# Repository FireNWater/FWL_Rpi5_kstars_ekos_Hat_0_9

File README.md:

# Raspberry Pi Hat for AstroArch Version 0.9

This repository is for a Raspberry Pi Hat that provides various hardware control functions for Astrophotography equipment. 

Currently this repository only contains the KiCAD files, but I will add more photos and instructions to build your own as I progress.

Here is the link to order PCBs at OshPark:  https://oshpark.com/shared_projects/S5zMuqNM

This is the link to DigiKey Parts List: https://www.digikey.com/en/mylists/list/DTLNYIF8ZV

The DigiKey list includes 10% attrition, so depending on how good you think you are you can save a bit of money there.

The files in the "Linux Software" folder are system files and aliases to help you control the various functions of the hat.  The systemd files are written so that all of the DC power ports and Dew Heater ports turn on once the Raspberry Pi has completed its boot up.  The udev rules will allow you to control the Rpi GPIO ports from the terminal without using sudo.  The aliases, are shortcuts to turning the DC power ports and Dew Heaters on and off from a terminal.

The "libgpiod" package must be installed in order to control the GPIO pins from the command line.  To install in Arch Linux type: "sudo pacman -S libgpiod" at the command line.

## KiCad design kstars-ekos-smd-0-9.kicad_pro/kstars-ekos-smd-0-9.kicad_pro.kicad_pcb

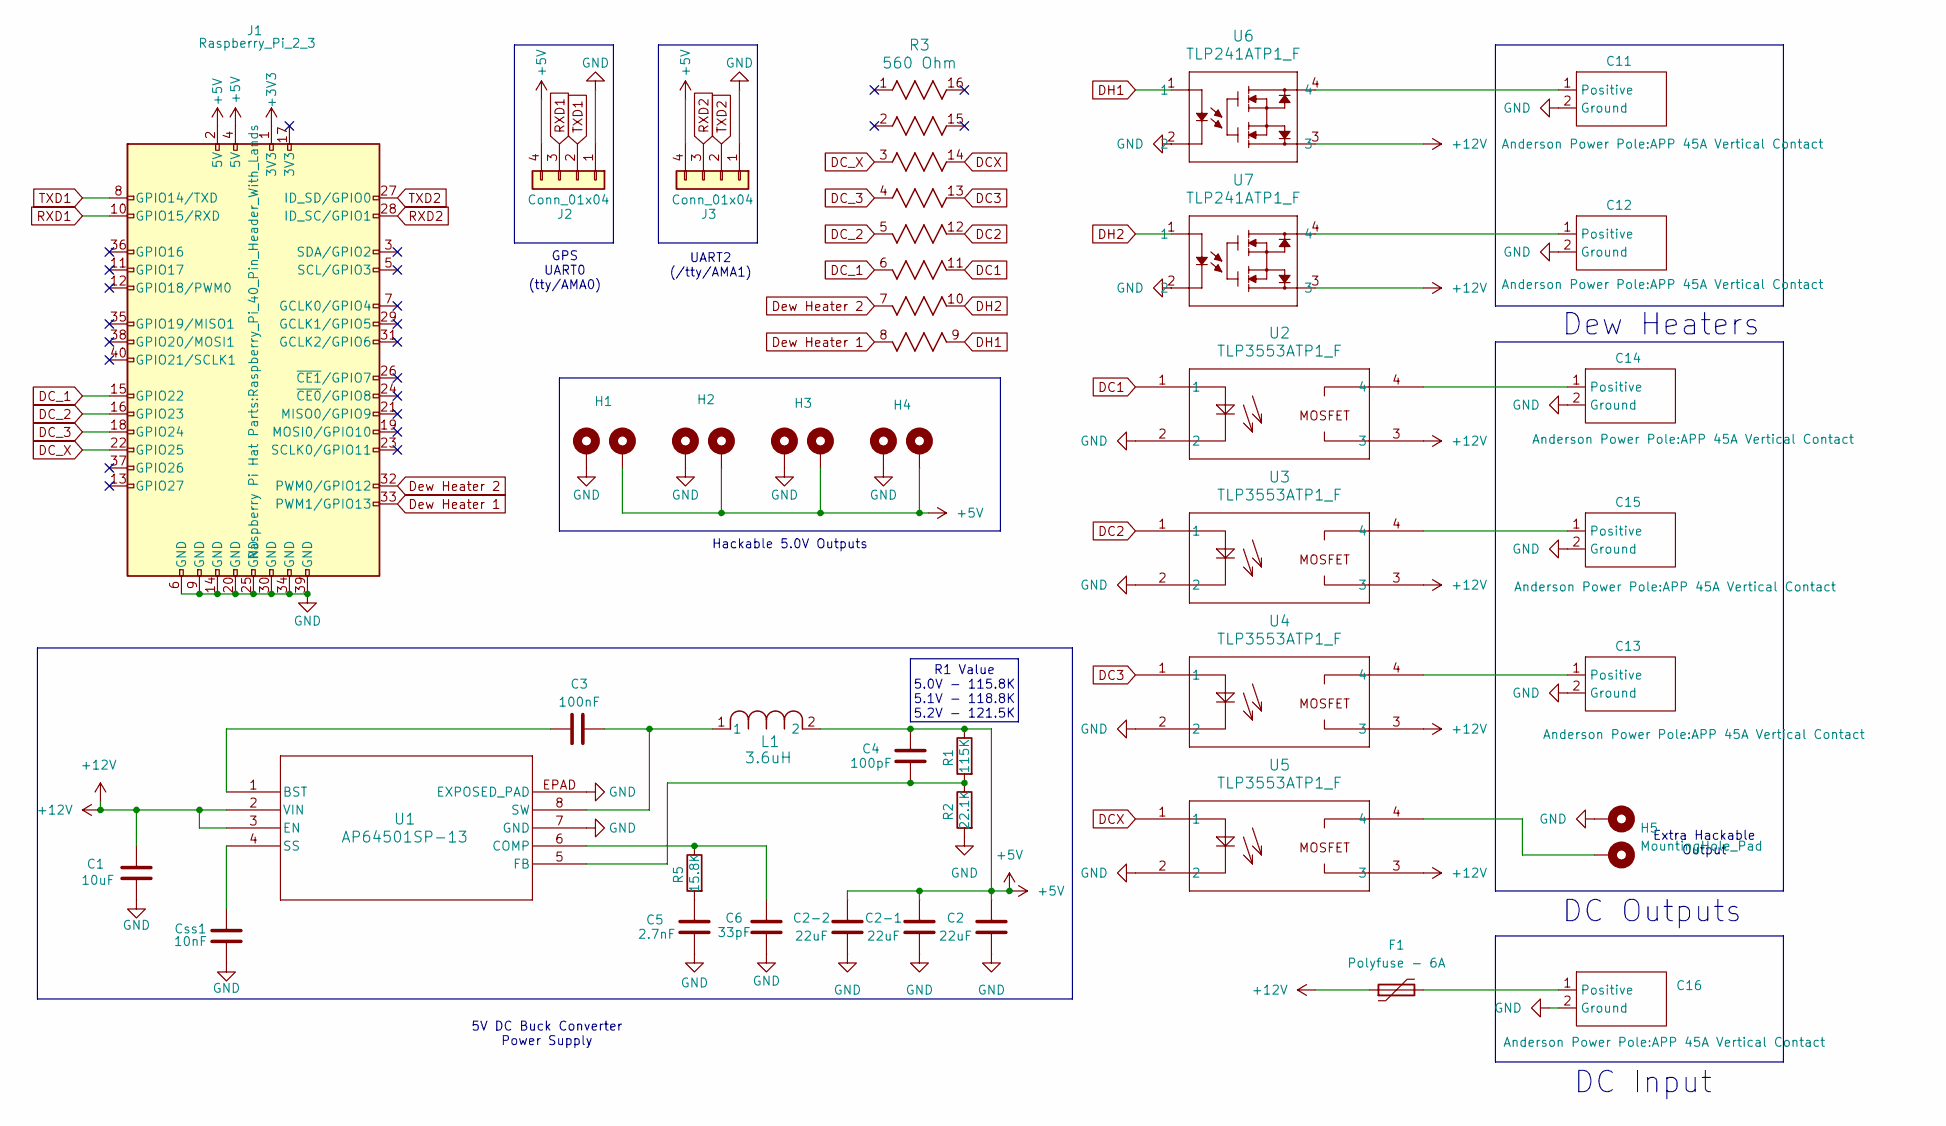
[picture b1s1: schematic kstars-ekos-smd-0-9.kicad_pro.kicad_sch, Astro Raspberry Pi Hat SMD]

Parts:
C1: 10uF; C_0805_2012Metric
C2, C2-1, C2-2: 22uF; C_0805_2012Metric
C3: 100nF; C_0805_2012Metric
C4: 100pF; C_0805_2012Metric
C5: 2.7nF; C_0805_2012Metric
C6: 33pF; C_0805_2012Metric
C11, C12, C13, C14, C15, C16: APP 45A Vertical Contact
Css1: 10nF; C_0805_2012Metric
F1: Polyfuse - 6A; Fuse_2920_7451Metric
H1, H2, H3, H4, H5: MountingHole_Pad; PinHeader_1x02_P2.54mm_Vertical
J1: Raspberry_Pi_2_3; Raspberry_Pi_40_Pin_Header_With_Lands
J2, J3: Conn_01x04; PinHeader_1x04_P2.54mm_Vertical
L1: 3.6uH; L_Cenker_CKCS8080
R1: 115K; R_0805_2012Metric
R2: 22.1K; R_0805_2012Metric
R3: 560 Ohm; RES_EXB2HV
R5: 15.8K; R_0805_2012Metric
U1: AP64501SP-13; SO-8EP_DIO
U2, U3, U4, U5: TLP3553ATP1_F; SOIC_3553ATP1_F_TOS
U6, U7: TLP241ATP1_F; SOIC_3553ATP1_F_TOS

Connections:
+3V3: J1.1 (3V3)
+5V: C2.2, C2-1.2, C2-2.2, C4.1, H1.2, H2.2, H3.2, H4.2, J1.2 (5V), J1.4 (5V), J2.4, J3.4, L1.2, R1.2
+12V: C1.2, F1.1, U1.2 (VIN), U1.3 (EN), U2.3, U3.3, U4.3, U5.3, U6.3, U7.3
DC1: R3.11, U2.1
DC2: R3.12, U3.1
DC3: R3.13, U4.1
DCX: R3.14, U5.1
DC_1: J1.15 (GPIO22), R3.6
DC_2: J1.16 (GPIO23), R3.5
DC_3: J1.18 (GPIO24), R3.4
DC_X: J1.22 (GPIO25), R3.3
DH1: R3.9, U6.1
DH2: R3.10, U7.1
Dew Heater 1: J1.33 (PWM1/GPIO13), R3.8
Dew Heater 2: J1.32 (PWM0/GPIO12), R3.7
GND: C1.1, C2.1, C2-1.1, C2-2.1, C5.2, C6.2, C11.2 (Ground), C12.2 (Ground), C13.2 (Ground), C14.2 (Ground), C15.2 (Ground), C16.2 (Ground), Css1.2, H1.1, H2.1, H3.1, H4.1, H5.1, J1.6 (GND), J1.9 (GND), J1.14 (GND), J1.20 (GND), J1.25 (GND), J1.30 (GND), J1.34 (GND), J1.39 (GND), J2.1, J3.1, R2.1, U1.7 (GND), U1.EPAD (EXPOSED_PAD), U2.2, U3.2, U4.2, U5.2, U6.2, U7.2
unnamed: C5.1, R5.1
unnamed: C11.1 (Positive), U6.4
unnamed: C12.1 (Positive), U7.4
unnamed: C13.1 (Positive), U4.4
unnamed: C14.1 (Positive), U2.4
unnamed: C15.1 (Positive), U3.4
unnamed: C16.1 (Positive), F1.2
unnamed: H5.2, U5.4
unnamed: C3.1, U1.1 (BST)
unnamed: C6.1, R5.2, U1.6 (COMP)
unnamed: C4.2, R1.1, R2.2, U1.5 (FB)
unnamed: Css1.1, U1.4 (SS)
unnamed: C3.2, L1.1, U1.8 (SW)
RXD1: J1.10 (GPIO15/RXD), J2.3
RXD2: J1.28 (ID_SC/GPIO1), J3.3
TXD1: J1.8 (GPIO14/TXD), J2.2
TXD2: J1.27 (ID_SD/GPIO0), J3.2

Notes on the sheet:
GPS UART0 (tty/AMA0)
5V DC Buck Converter Power Supply
UART2 (/tty/AMA1)
R1 Value 5.0V - 115.8K 5.1V - 118.8K 5.2V - 121.5K
Dew Heaters
Extra Hackable Output
DC Outputs
DC Input
Hackable 5.0V Outputs

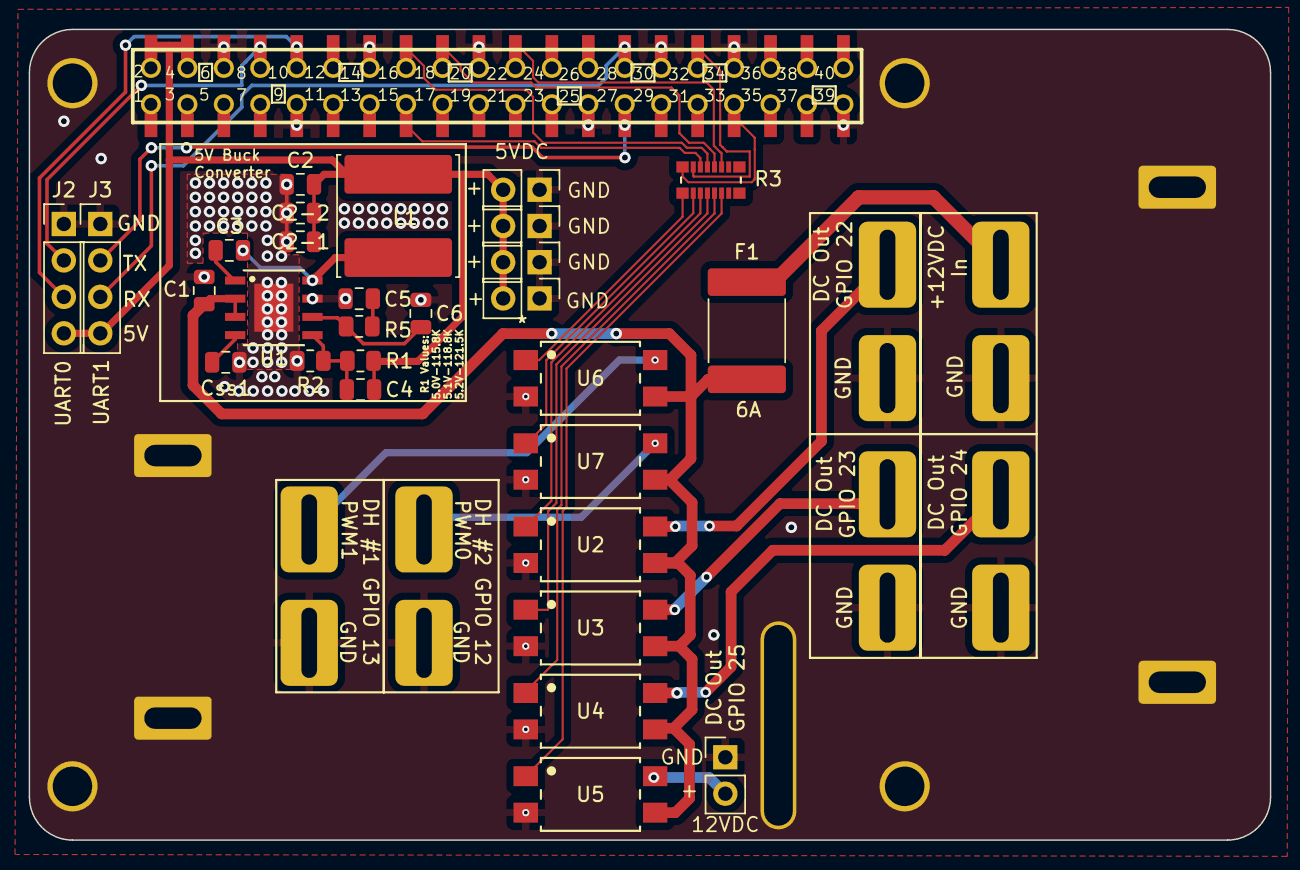
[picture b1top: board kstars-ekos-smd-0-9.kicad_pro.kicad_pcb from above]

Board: 2 copper layers, 86.5 x 56.5 mm, 36 parts (0 on the bottom side), 32 nets.

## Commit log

2025-06-05 Add files via upload
    Added copper flood to front and additional cooling vias.
2025-06-06 Final design submitted to fab.
2025-06-06 Corrected hole locations. Final upload to fab.
2025-07-08 Updated 40-pin numbering silkscreen.
2025-07-10 Update README.md
    Added PCB and DigiKey parts list.
2025-07-28 Fixed GPIO16 trace . .
2025-07-28 Connected GPIO 16 trace . .
2025-07-28 Fixed GPIO 16 trace
2025-07-28 Update README.md
    Updated PCB design.
2025-08-08 added Terminal commands
2025-08-08 Edited Readme
2025-08-18 Terminal menu and gpio control. . .
2025-08-19 Minor changes to menu
2025-08-19 Minor code edit
2025-08-19 Removed an unnecessary .tar.gz filez
